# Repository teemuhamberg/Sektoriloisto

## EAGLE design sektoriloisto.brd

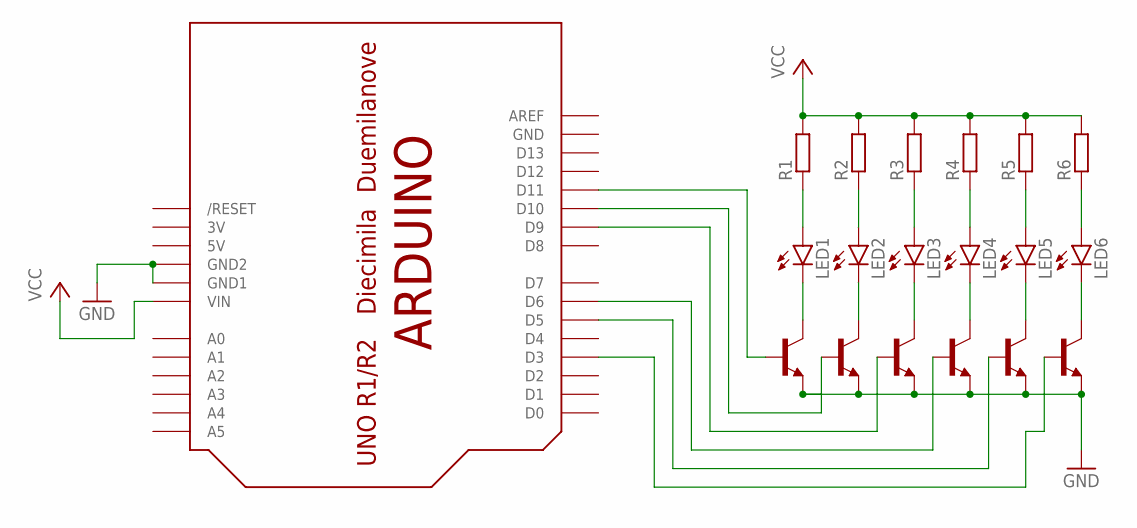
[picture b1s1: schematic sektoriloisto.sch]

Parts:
LED1, LED2, LED3, LED4, LED5, LED6: LED5MM
Q1, Q2, Q3, Q4, Q5, Q6: BC548A; TO92-EBC
R1, R2, R3, R4, R5, R6: R-EU_0207/10; 0207/10
U$1: ARDUINO-NOHOLE

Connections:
3V: U$1.3V
5V: U$1.5V
GND: Q1.E, Q2.E, Q3.E, Q4.E, Q5.E, Q6.E, U$1.GND, U$1.GND1, U$1.GND2
unnamed: LED1.K (C), Q1.C
unnamed: LED1.A, R1.1
unnamed: LED2.A, R2.1
unnamed: LED3.A, R3.1
unnamed: LED4.A, R4.1
unnamed: LED5.A, R5.1
unnamed: LED6.A, R6.1
unnamed: LED2.K (C), Q2.C
unnamed: LED3.K (C), Q3.C
unnamed: LED4.K (C), Q4.C
unnamed: LED5.K (C), Q5.C
unnamed: LED6.K (C), Q6.C
unnamed: Q4.B, U$1.D6
unnamed: Q1.B, U$1.D11
unnamed: Q2.B, U$1.D10
unnamed: Q3.B, U$1.D9
unnamed: Q5.B, U$1.D5
unnamed: Q6.B, U$1.D3
VCC: R1.2, R2.2, R3.2, R4.2, R5.2, R6.2, U$1.VIN

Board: 2 copper layers, 19 parts (0 on the bottom side), 20 nets, no tracks yet.
